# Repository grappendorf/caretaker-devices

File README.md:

Caretaker Smart Home Server Devices
===================================

Caretaker is a DIY smart home project. The aim is to create a totally wireless and scaleable system to control 
power switches (lamps and other electrical appliances) and measure values like temperatures, brightness and power 
consumption. All devices should be controllable through local devices as well as mobile devices over the internet. 
The goal is to use WiFly WLAN modules in every device. This allows for a bi-directional communication between all 
devices, so besides controlling a device it can itself send asynchronous status update messages, i.e. pressing a 
physical button on a dimmer to switch a lamp on, will also update a button in a remote control application, 
eliminating the need for periodically polling the device status

This project contains the firmware and Eagle PCB schematics and layouts for the various Caretaker devices.

Licenses
--------

The firmare source code is licensed under the MIT license.
The hardware is licensed under the CERN Open Hardware Licence v1.2.

Third Party Libraries
----------------------

The following Arduino libraries are included into this project:

* Adafruit_MAX31855
	https://github.com/adafruit/Adafruit-MAX31855-library
	BSD
* Bounce 
  http://www.arduino.cc/playground/Code/Bounce  
  LGPL3
* ClickEncoder
  https://github.com/0xPIT/encoder
  MIT
* CmdMessenger
  http://playground.arduino.cc//Code/CmdMessenger
  MIT
* DallasTemperature
  http://milesburton.com/Dallas_Temperature_Control_Library   
  GPL2 
* EasyVr
	https://github.com/RoboTech-srl/EasyVR-Arduino
	MIT
* EEPROMex
  http://thijs.elenbaas.net/2012/07/extended-eeprom-library-for-arduino/
  LGPL
* LiquidCrystal440
  https://code.google.com/p/liquidcrystal440/
  GPL3
* MultiMap
  http://playground.arduino.cc/Main/MultiMap
  MIT?
* OneWire
  http://www.pjrc.com/teensy/td_libs_OneWire.html
  CUSTOM
* PID
  http://playground.arduino.cc/Code/PIDLibrary
  GPL3
* PinChangeInt
  http://arduino.cc/playground/Main/PinChangeInt
  GPL3
* RunningAverage
  http://playground.arduino.cc/Main/runningAverage
  MIT?
* TimerOne
  http://arduino.cc/playground/Code/Timer1
  GPL3
* WiFly
	https://github.com/Seeed-Studio/WiFi_Shield
	MIT?

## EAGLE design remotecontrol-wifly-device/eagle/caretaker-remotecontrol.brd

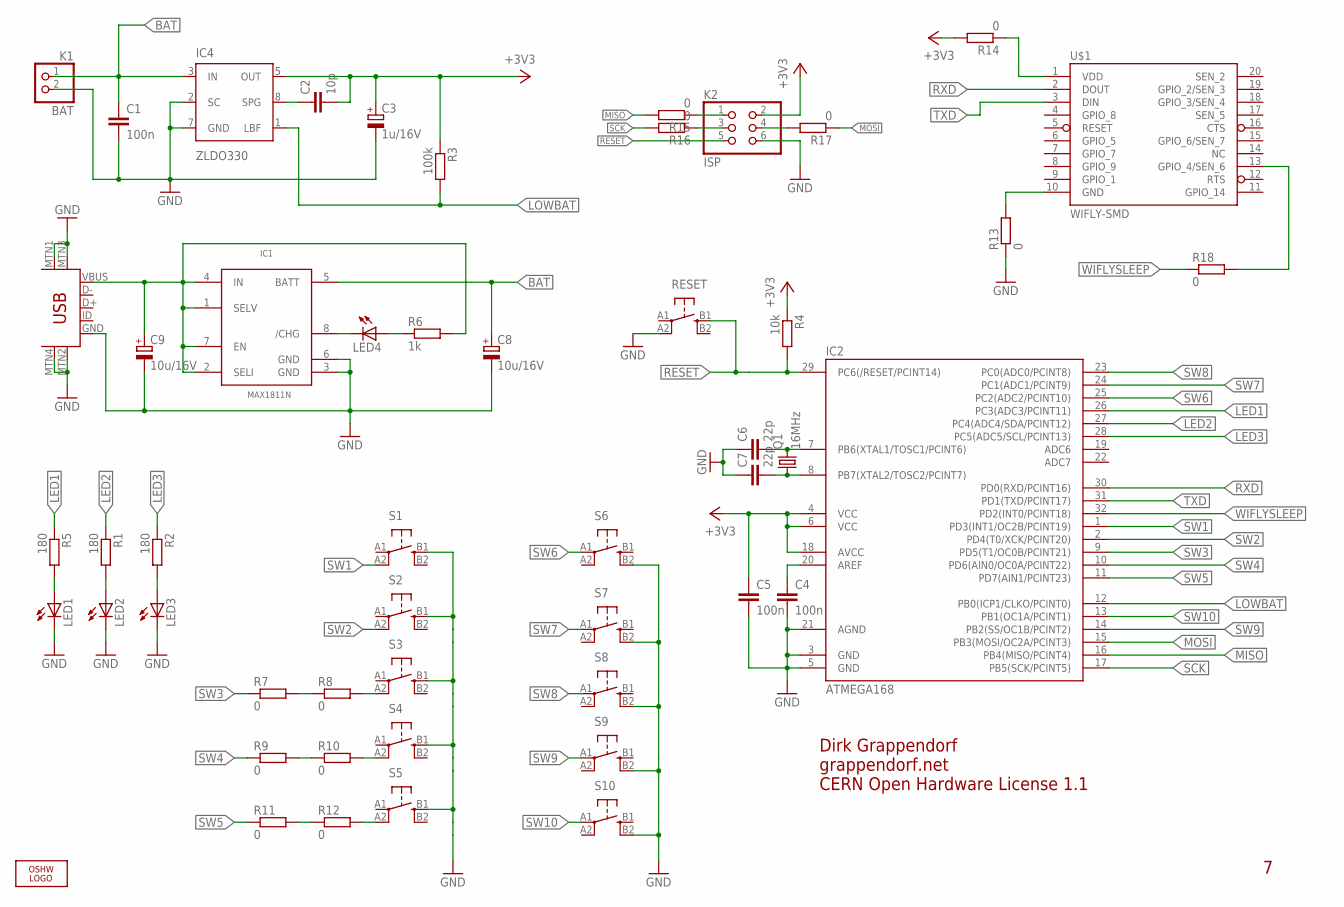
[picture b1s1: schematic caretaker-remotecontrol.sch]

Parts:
C1, C4, C5: 100n; C1206
C2: 10p; C1206
C3: 1u/16V; PANASONIC_B
C6, C7: 22p; C1206
C8, C9: 10u/16V; PANASONIC_B
IC1: MAX1811N; SO08
IC2: ATMEGA168; TQFP32-08
IC4: ZLDO330; SM8
K1: BAT; 1X02
K2: ISP; 2X03/90
K3: USB-MINIB-5PIN; USB-MINIB
LED1, LED2, LED3, LED4: LEDKA-3528ASYC; KA-3528ASYC
LOGO1: OSHW_LOGO_10MILX0350-NT; OSHW_10X350_NOTEXT
Q1: 16MHz; HC49UP
R1, R2, R5: 180; R1206
R3: 100k; R1206
R4: 10k; R1206
R6: 1k; R1206
R7, R8, R9, R10, R11, R12, R13, R14, R15, R16, R17, R18: 0; R1206
RESET: TAC_SWITCHSMD-BIG; TACTILE_SWITCH_TALL
S1, S2, S3, S4, S5, S6, S7, S8, S9, S10: TAC_SWITCHSMD-BIG; TACTILE_SWITCH_TALL
U$1: WIFLY-SMD

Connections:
+3V3: C2.2, C3.+, C5.1, IC2.4 (VCC), IC2.6 (VCC), IC2.18 (AVCC), IC4.5 (OUT), K2.2, R3.1, R4.1, R14.2
BAT: C1.1, C8.+, IC1.5 (BATT), IC4.3 (IN), K1.1
GND: C1.2, C3.-, C4.2, C5.2, C6.1, C7.1, C8.-, C9.-, IC1.3 (GND), IC1.6 (GND), IC2.3 (GND), IC2.5 (GND), IC2.21 (AGND), IC4.2 (SC), IC4.7 (GND), K1.2, K2.6, K3.GND, K3.MTN1 (MTN2), K3.MTN2 (MTN3), K3.MTN3 (MTN1), K3.MTN4, LED1.C, LED2.C, LED3.C, R13.1, RESET.A2 (2), S1.B1 (3), S2.B1 (3), S3.B1 (3), S4.B1 (3), S5.B1 (3), S6.B2 (4), S7.B2 (4), S8.B2 (4), S9.B2 (4), S10.B2 (4)
LED1: IC2.26 (PC3(ADC3/PCINT11)), R5.1
LED2: IC2.27 (PC4(ADC4/SDA/PCINT12)), R1.1
LED3: IC2.28 (PC5(ADC5/SCL/PCINT13)), R2.1
LOWBAT: IC2.12 (PB0(ICP1/CLKO/PCINT0)), IC4.1 (LBF), R3.2
MISO: IC2.16 (PB4(MISO/PCINT4)), R15.2
MOSI: IC2.15 (PB3(MOSI/OC2A/PCINT3)), R17.1
unnamed: C9.+, IC1.1 (SELV), IC1.2 (SELI), IC1.4 (IN), IC1.7 (EN), K3.VBUS, R6.2
unnamed: C4.1, IC2.20 (AREF)
unnamed: C6.2, IC2.7 (PB6(XTAL1/TOSC1/PCINT6)), Q1.2
unnamed: C7.2, IC2.8 (PB7(XTAL2/TOSC2/PCINT7)), Q1.1
unnamed: LED2.A, R1.2
unnamed: LED3.A, R2.2
unnamed: LED4.A, R6.1
unnamed: LED1.A, R5.2
unnamed: IC1.8 (/CHG), LED4.C
unnamed: C2.1, IC4.8 (SPG)
unnamed: R8.2, S3.A2 (2)
unnamed: R10.2, S4.A2 (2)
unnamed: R12.2, S5.A2 (2)
unnamed: R7.2, R8.1
unnamed: R9.2, R10.1
unnamed: R11.2, R12.1
unnamed: R13.2, U$1.10 (GND)
unnamed: R14.1, U$1.1 (VDD)
unnamed: K2.1, R15.1
unnamed: K2.3, R16.1
unnamed: K2.4, R17.2
unnamed: R18.2, U$1.13 (GPIO_4/SEN_6)
RESET: IC2.29 (PC6(/RESET/PCINT14)), K2.5, R4.2, RESET.B1 (3)
RXD: IC2.30 (PD0(RXD/PCINT16)), U$1.2 (DOUT)
SCK: IC2.17 (PB5(SCK/PCINT5)), R16.2
SW1: IC2.1 (PD3(INT1/OC2B/PCINT19)), S1.A2 (2)
SW2: IC2.2 (PD4(T0/XCK/PCINT20)), S2.A2 (2)
SW3: IC2.9 (PD5(T1/OC0B/PCINT21)), R7.1
SW4: IC2.10 (PD6(AIN0/OC0A/PCINT22)), R9.1
SW5: IC2.11 (PD7(AIN1/PCINT23)), R11.1
SW6: IC2.25 (PC2(ADC2/PCINT10)), S6.A1 (1)
SW7: IC2.24 (PC1(ADC1/PCINT9)), S7.A1 (1)
SW8: IC2.23 (PC0(ADC0/PCINT8)), S8.A1 (1)
SW9: IC2.14 (PB2(SS/OC1B/PCINT2)), S9.A1 (1)
SW10: IC2.13 (PB1(OC1A/PCINT1)), S10.A1 (1)
TXD: IC2.31 (PD1(TXD/PCINT17)), U$1.3 (DIN)
WIFLYSLEEP: IC2.32 (PD2(INT0/PCINT18)), R18.1

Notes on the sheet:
Dirk Grappendorf
grappendorf.net
CERN Open Hardware License 1.1

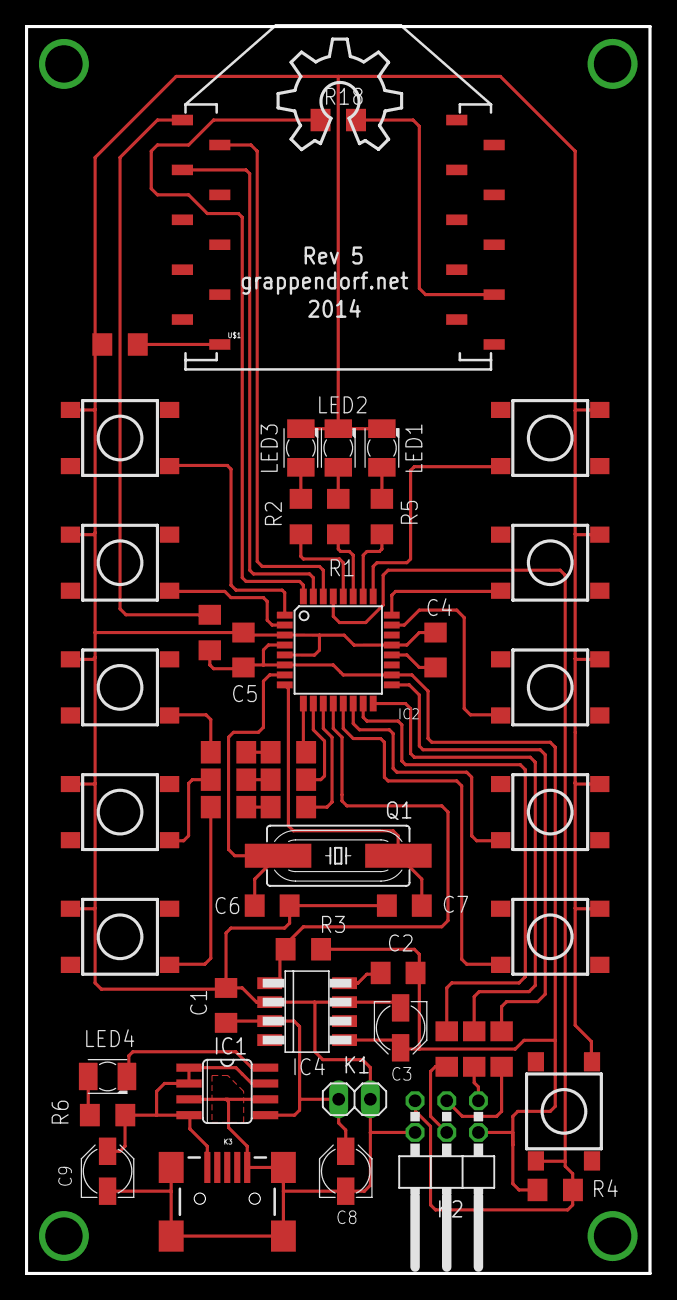
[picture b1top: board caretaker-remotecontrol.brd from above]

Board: 2 copper layers, 50.0 x 100.0 mm, 51 parts (0 on the bottom side), 46 nets.

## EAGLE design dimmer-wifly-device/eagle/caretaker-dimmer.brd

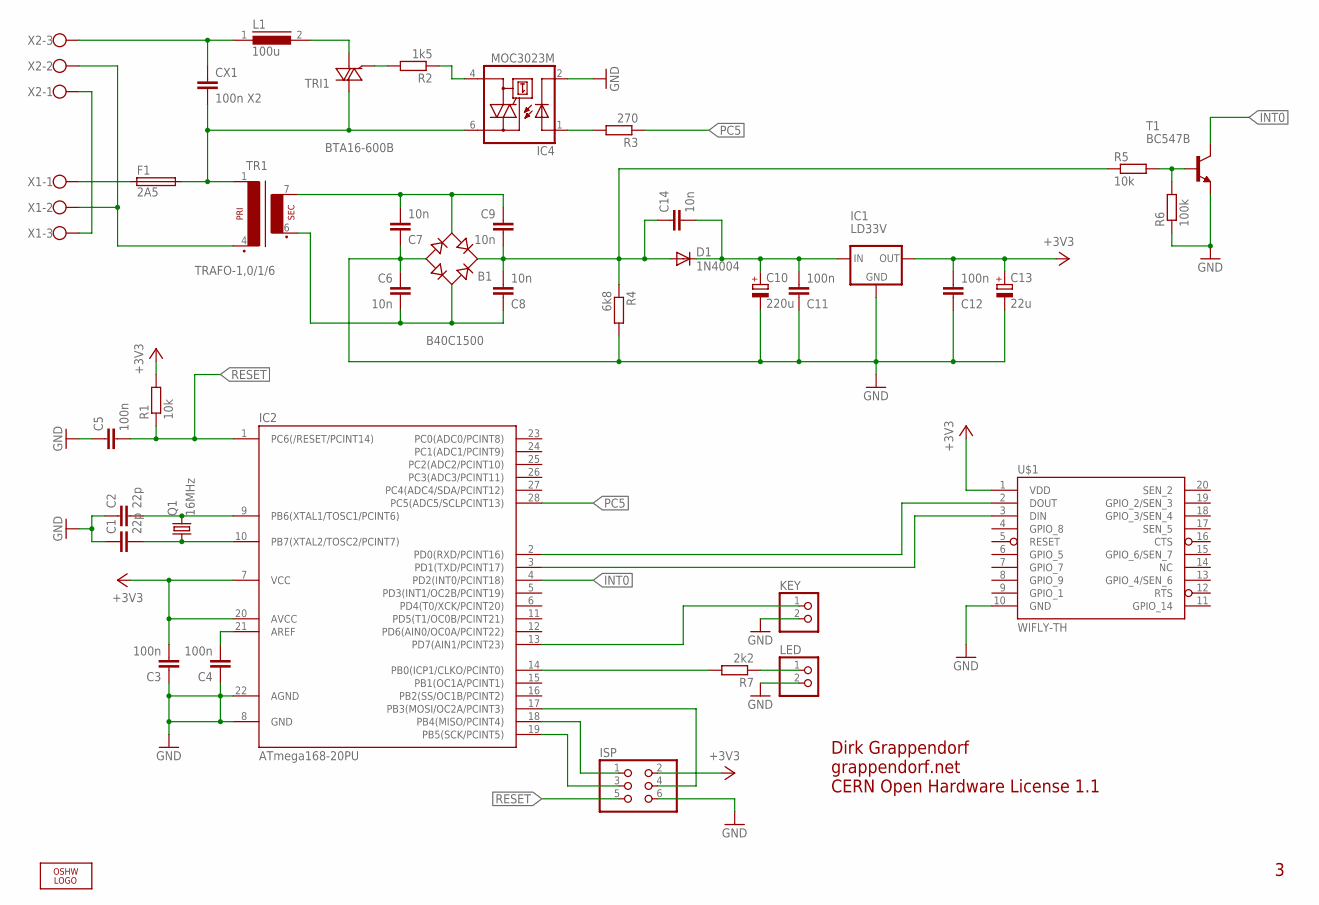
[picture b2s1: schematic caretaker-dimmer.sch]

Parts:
B1: B40C1500; 2KBB
C1, C2: 22p; C025-025X050
C3, C4, C5, C11, C12: 100n; C025-024X044
C6, C7, C8, C9, C14: 10n; C025-024X044
C10: 220u; E3,5-8
C13: 22u; E2,5-5
CX1: 100n X2; XC15B10
D1: 1N4004; D-10
F1: 2A5; SH22,5
IC1: LD33V; 78XXL
IC2: ATmega168-20PU; DIL28-3
IC4: MOC3023M; DIL06
ISP: PINHD-2X3; 2X03
KEY: PINHD-1X2; 1X02
L1: 100u; ED22
LED: PINHD-1X2; 1X02
LOGO1: OSHW_LOGO_10MILX0350-NT-BOTTOM; OSHW_10X350_NOTEXT_BOTTOM
Q1: 16MHz; HC49U-V
R1, R5: 10k; 0204/7
R2: 1k5; 0204/7
R3: 270; 0204/7
R4: 6k8; 0204/7
R6: 100k; 0204/7
R7: 2k2; 0204/7
T1: BC547B; TO92
TR1: TRAFO-1,0/1/6
TRI1: BTA16-600B; TO220AB
U$1: WIFLY-TH
X1, X2: W237-103

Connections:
+3V3: C3.2, C12.2, C13.+, IC1.GND (OUT), IC2.7 (VCC), IC2.20 (AVCC), ISP.2, R1.2, U$1.1 (VDD)
GND: B1.-, C1.1, C2.1, C3.1, C4.1, C5.1, C6.1, C7.1, C10.-, C11.1, C12.1, C13.-, IC1.IN (GND), IC2.8 (GND), IC2.22 (AGND), IC4.2 (C), ISP.6, KEY.2, LED.2, R4.2, R6.1, T1.1 (E), U$1.10 (GND)
INT0: IC2.4 (PD2(INT0/PCINT18)), T1.3 (C)
unnamed: C2.2, IC2.9 (PB6(XTAL1/TOSC1/PCINT6)), Q1.2
unnamed: C1.2, IC2.10 (PB7(XTAL2/TOSC2/PCINT7)), Q1.1
unnamed: C4.2, IC2.21 (AREF)
unnamed: LED.1, R7.1
unnamed: B1.AC1, C6.2, C8.1, TR1.6 (S3)
unnamed: R2.2, TRI1.3 (G)
unnamed: C10.+, C11.2, C14.2, D1.C, IC1.OUT (IN)
unnamed: B1.AC2, C7.2, C9.1, TR1.7 (S4)
unnamed: CX1.1, L1.1, X2.3
unnamed: F1.1, X1.1
unnamed: L1.2, TRI1.1 (A1)
unnamed: CX1.2, F1.2, IC4.6 (A2), TR1.1, TRI1.2 (A2)
unnamed: TR1.4 (P2), X1.2, X2.2
unnamed: IC4.4 (A1), R2.1
unnamed: IC4.1 (A), R3.2
unnamed: IC2.2 (PD0(RXD/PCINT16)), U$1.2 (DOUT)
unnamed: IC2.13 (PD7(AIN1/PCINT23)), KEY.1
unnamed: R5.2, R6.2, T1.2 (B)
unnamed: IC2.18 (PB4(MISO/PCINT4)), ISP.1
unnamed: IC2.19 (PB5(SCK/PCINT5)), ISP.3
unnamed: IC2.17 (PB3(MOSI/OC2A/PCINT3)), ISP.4
unnamed: IC2.14 (PB0(ICP1/CLKO/PCINT0)), R7.2
unnamed: X1.3, X2.1
unnamed: IC2.3 (PD1(TXD/PCINT17)), U$1.3 (DIN)
unnamed: B1.+, C8.2, C9.2, C14.1, D1.A, R4.1, R5.1
PC5: IC2.28 (PC5(ADC5/SCLPCINT13)), R3.1
RESET: C5.2, IC2.1 (PC6(/RESET/PCINT14)), ISP.5, R1.1

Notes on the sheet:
Dirk Grappendorf
grappendorf.net
CERN Open Hardware License 1.1

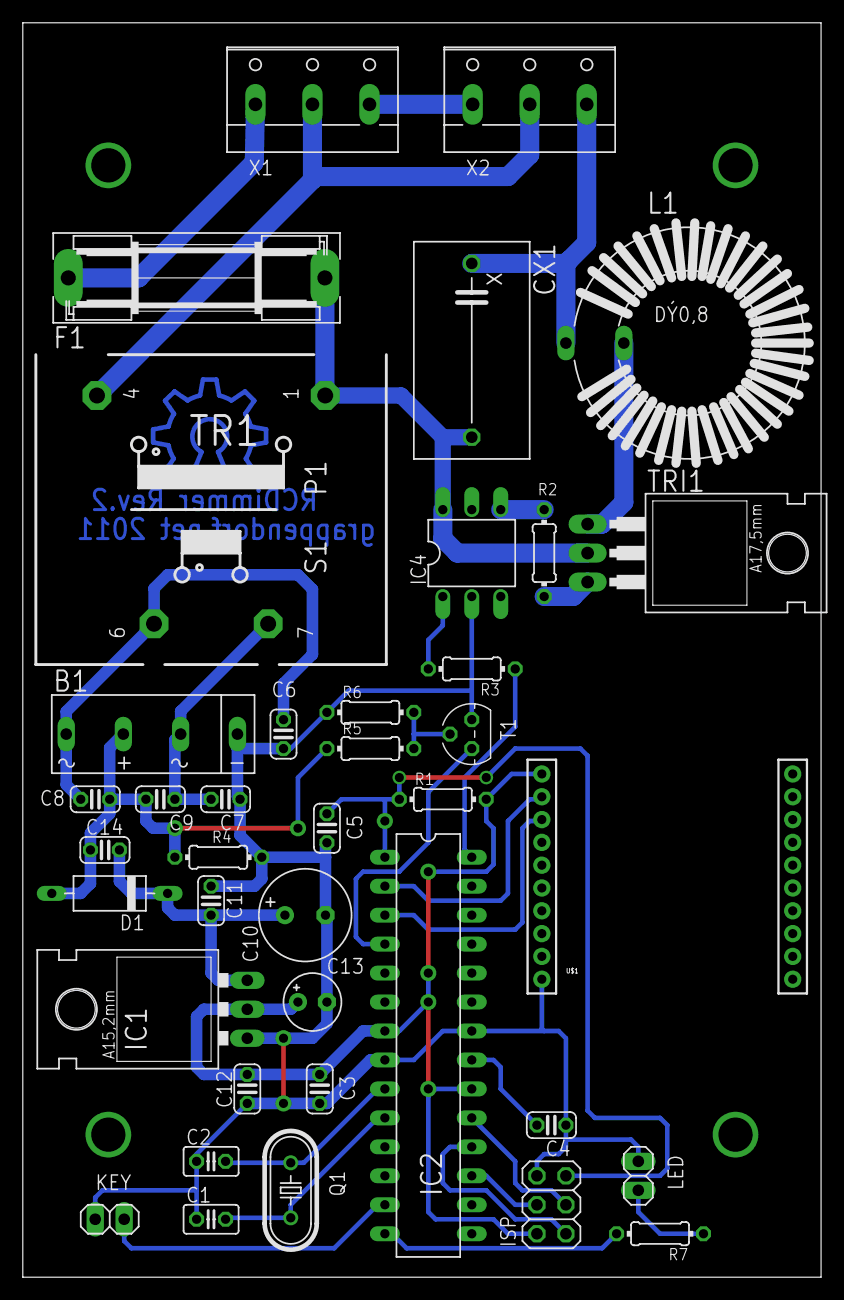
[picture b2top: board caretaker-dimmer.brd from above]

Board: 2 copper layers, 70.0 x 110.0 mm, 40 parts (0 on the bottom side), 30 nets.

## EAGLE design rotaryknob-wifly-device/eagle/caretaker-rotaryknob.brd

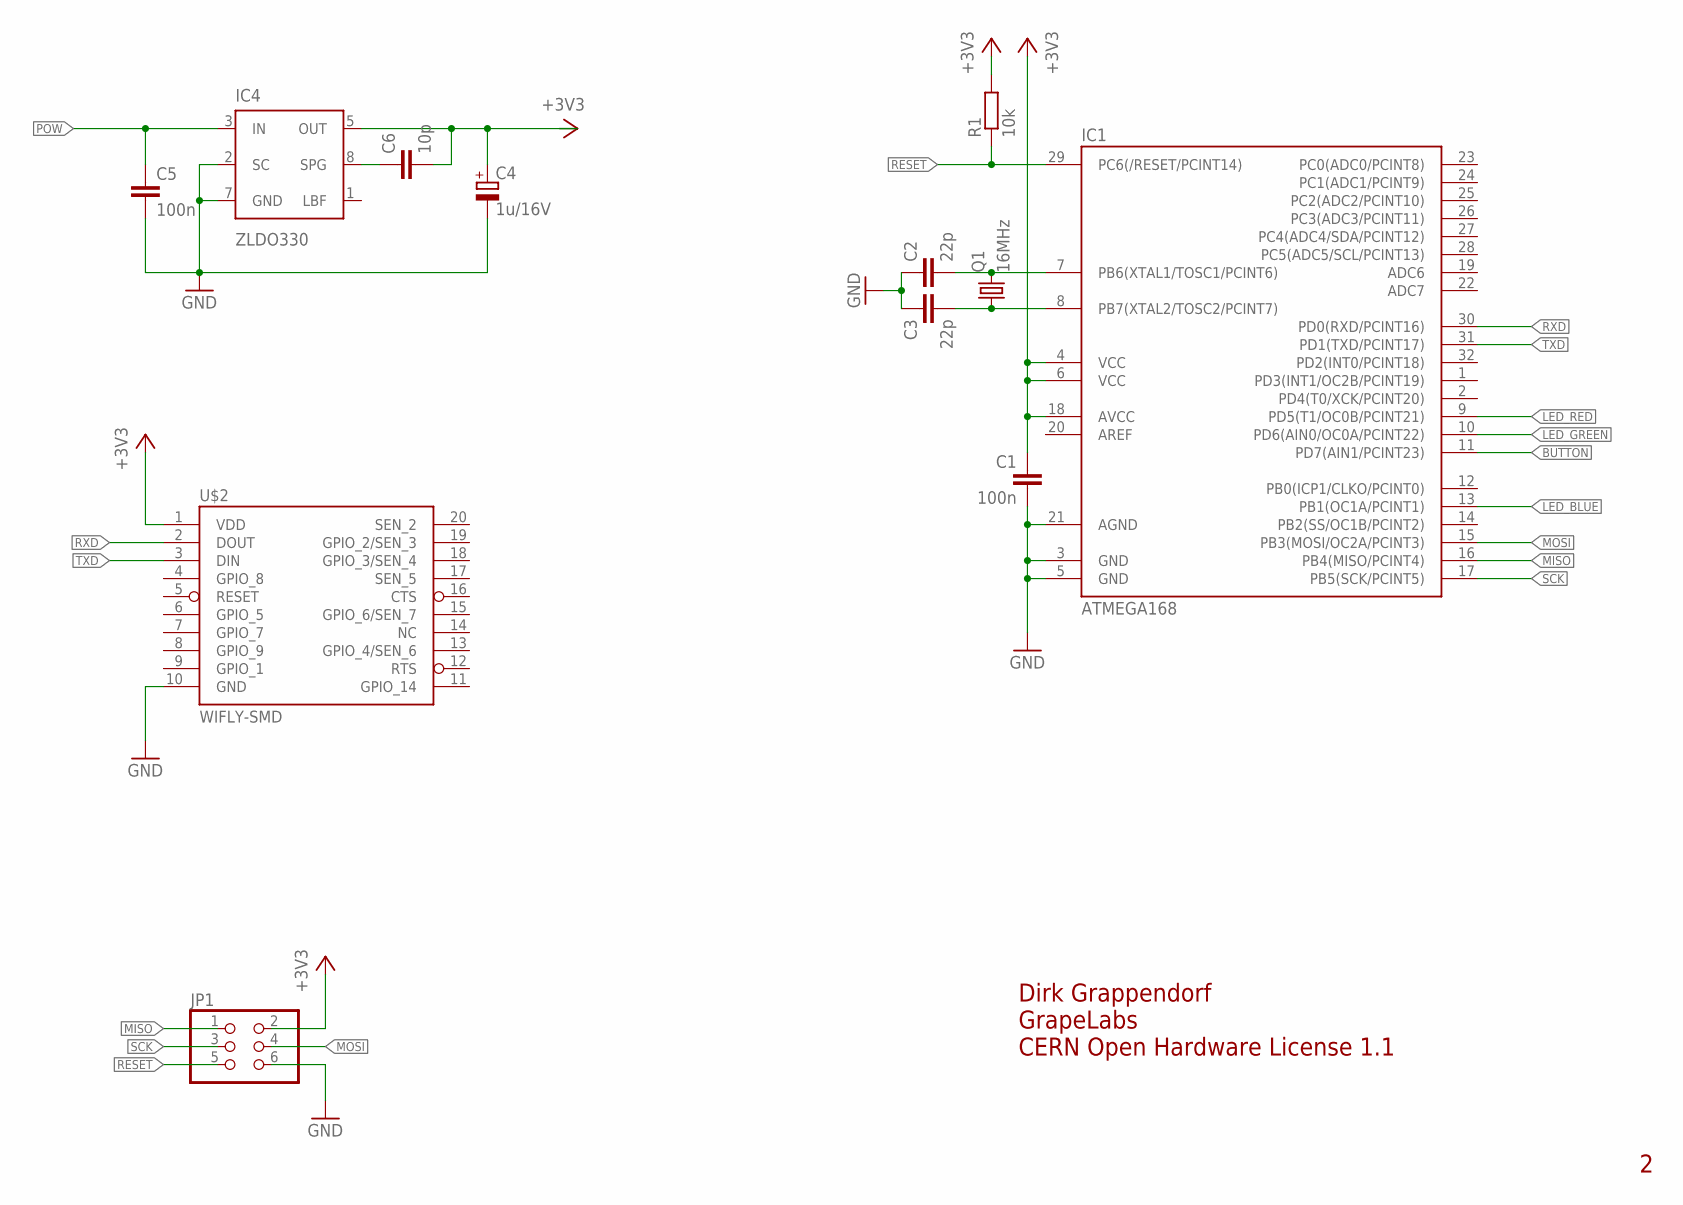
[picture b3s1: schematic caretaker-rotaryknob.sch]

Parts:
C1: 100n; C1206K
C2, C3: 22p; C1206K
C4: 1u/16V; PANASONIC_B
C5: 100n; C1206
C6: 10p; C1206
IC1: ATMEGA168; TQFP32-08
IC4: ZLDO330; SM8
JP1: PINHD-2X3_2.54-SMD; 2X03SMD
Q1: 16MHz; HC49UP
R1: 10k; M1206
U$2: WIFLY-SMD

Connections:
+3V3: C1.1, C4.+, C6.2, IC1.4 (VCC), IC1.6 (VCC), IC1.18 (AVCC), IC4.5 (OUT), JP1.2, R1.2, U$2.1 (VDD)
BUTTON: IC1.11 (PD7(AIN1/PCINT23))
GND: C1.2, C2.1, C3.1, C4.-, C5.2, IC1.3 (GND), IC1.5 (GND), IC1.21 (AGND), IC4.2 (SC), IC4.7 (GND), JP1.6, U$2.10 (GND)
LED_BLUE: IC1.13 (PB1(OC1A/PCINT1))
LED_GREEN: IC1.10 (PD6(AIN0/OC0A/PCINT22))
LED_RED: IC1.9 (PD5(T1/OC0B/PCINT21))
MISO: IC1.16 (PB4(MISO/PCINT4)), JP1.1
MOSI: IC1.15 (PB3(MOSI/OC2A/PCINT3)), JP1.4
unnamed: C2.2, IC1.7 (PB6(XTAL1/TOSC1/PCINT6)), Q1.2
unnamed: C3.2, IC1.8 (PB7(XTAL2/TOSC2/PCINT7)), Q1.1
unnamed: C6.1, IC4.8 (SPG)
POW: C5.1, IC4.3 (IN)
RESET: IC1.29 (PC6(/RESET/PCINT14)), JP1.5, R1.1
RXD: IC1.30 (PD0(RXD/PCINT16)), U$2.2 (DOUT)
SCK: IC1.17 (PB5(SCK/PCINT5)), JP1.3
TXD: IC1.31 (PD1(TXD/PCINT17)), U$2.3 (DIN)

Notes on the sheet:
Dirk Grappendorf
GrapeLabs
CERN Open Hardware License 1.1

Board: 2 copper layers, 12 parts (0 on the bottom side), 12 nets, no tracks yet.

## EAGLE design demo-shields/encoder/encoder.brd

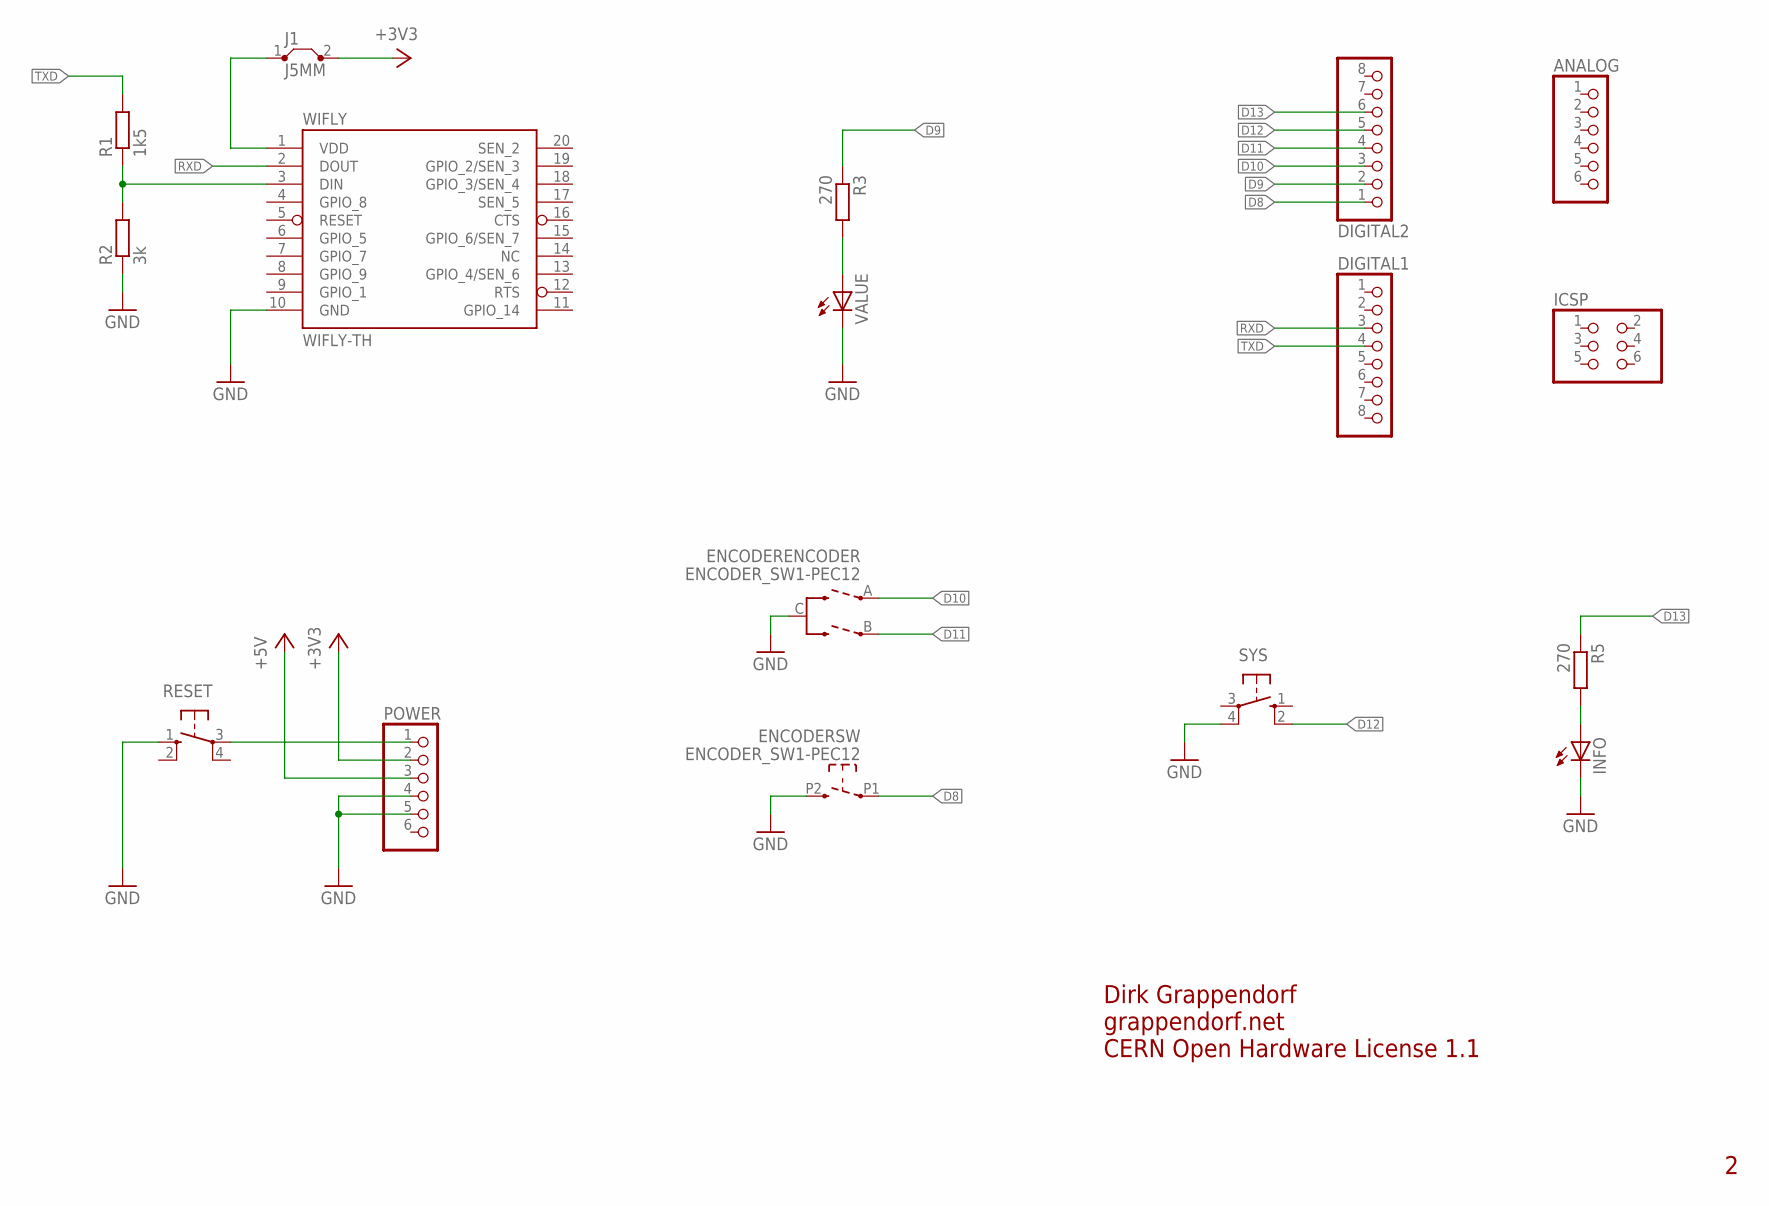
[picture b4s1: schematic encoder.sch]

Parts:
ANALOG: PINHD-1X6; 1X06
DIGITAL1: PINHD-1X8TH; 1X08-TH
DIGITAL2: PINHD-1X8_2.54; 1X08
ENCODER: ENCODER_SW1-PEC12; PEC12_INCREMENTAL_ENCODER
ICSP: PINHD-2X3; 2X03
INFO: LED3MM
J1: J5MM; 05
POWER: PINHD-1X6_2.54; 1X06
R1: 1k5; 0204/7
R2: 3k; 0204/7
R3, R5: 270; 0204/7
RESET: 10-XX; B3F-10XX
SYS: 10-XX; B3F-10XX
VALUE: LED3MM
WIFLY: WIFLY-TH

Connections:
+3V3: J1.2, POWER.2
+5V: POWER.3
D8: DIGITAL2.1, ENCODER.P1 (1)
D9: DIGITAL2.2, R3.1
D10: DIGITAL2.3, ENCODER.A
D11: DIGITAL2.4, ENCODER.B
D12: DIGITAL2.5, SYS.2 (S1)
D13: DIGITAL2.6, R5.1
GND: ENCODER.C, ENCODER.P2 (2), INFO.K (C), POWER.4, POWER.5, R2.1, RESET.1 (S), SYS.4 (P1), VALUE.K (C), WIFLY.10 (GND)
unnamed: R1.1, R2.2, WIFLY.3 (DIN)
unnamed: POWER.1, RESET.3
unnamed: J1.1, WIFLY.1 (VDD)
unnamed: R3.2, VALUE.A
unnamed: INFO.A, R5.2
RXD: DIGITAL1.3, WIFLY.2 (DOUT)
TXD: DIGITAL1.4, R1.2

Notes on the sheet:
Dirk Grappendorf
grappendorf.net
CERN Open Hardware License 1.1

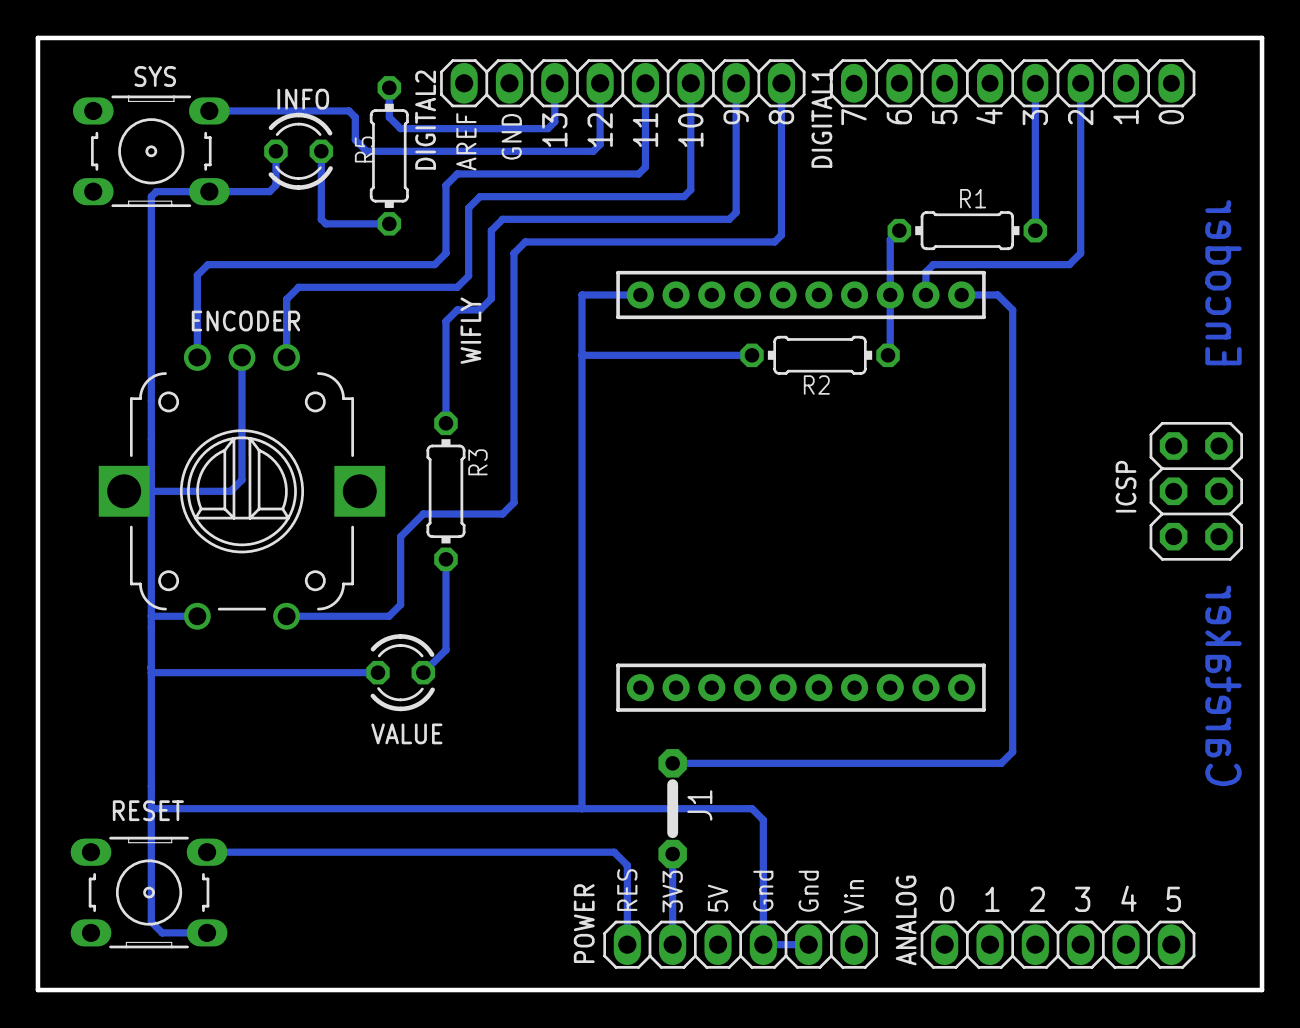
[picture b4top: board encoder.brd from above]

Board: 2 copper layers, 68.6 x 53.3 mm, 16 parts (0 on the bottom side), 15 nets.

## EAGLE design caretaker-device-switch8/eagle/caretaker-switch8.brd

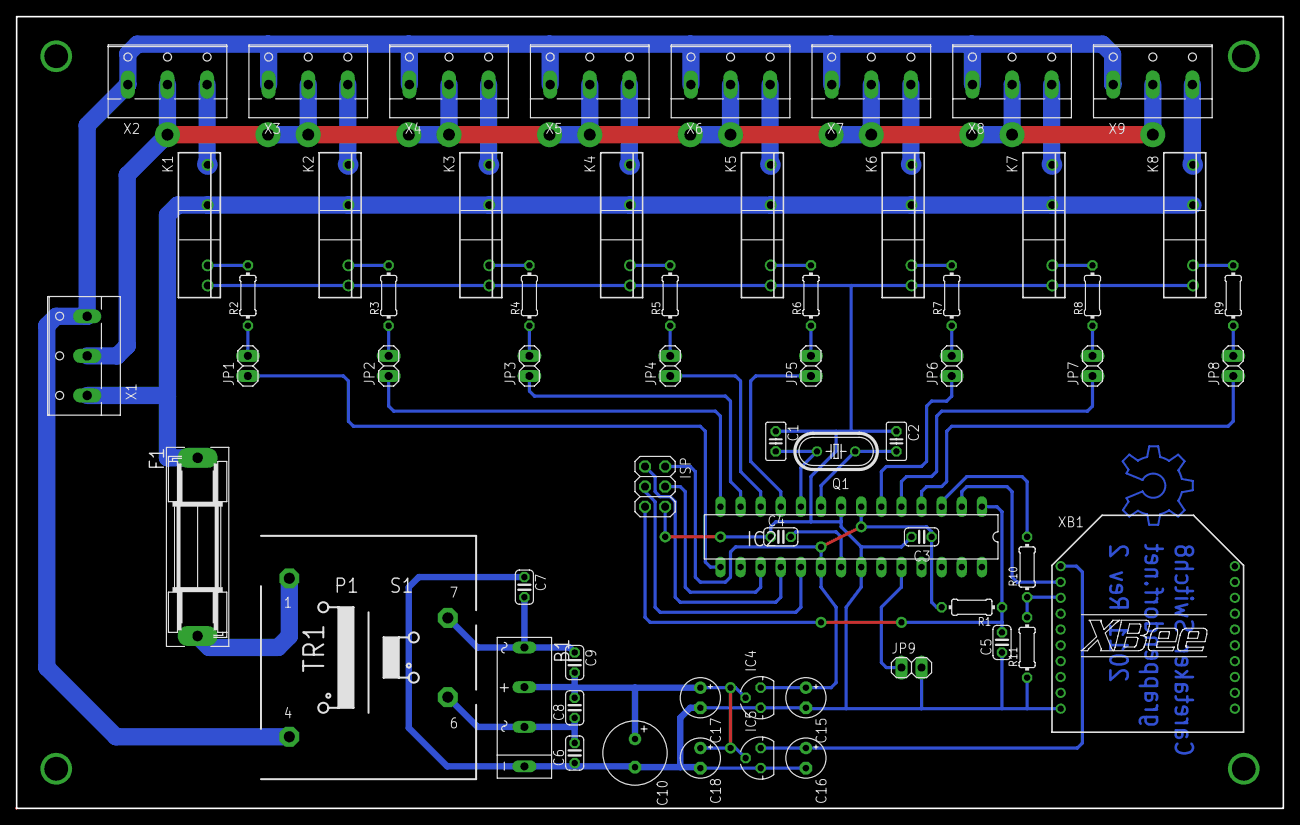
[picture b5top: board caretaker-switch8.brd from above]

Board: 2 copper layers, 160.0 x 100.0 mm, 61 parts (0 on the bottom side), 53 nets.

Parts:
B1: B40C1500; 2KBB
C1, C2: 22p; C025-025X050
C3, C4, C5: 100n; C025-024X044
C6, C7, C8, C9: 10n; C025-024X044
C10: 220u; E3,5-8
C15, C16, C17, C18: 1u; E2,5-5
F1: 2A; SH22,5
IC2: ATmega168-20PU; DIL28-3
IC4: MCP1702-5002; MCP1702
IC5: MCP1702-3302; MCP1702
ISP: 2X03
JP1: LED1; 1X02
JP2: LED2; 1X02
JP3: LED3; 1X02
JP4: LED4; 1X02
JP5: LED5; 1X02
JP6: LED6; 1X02
JP7: LED7; 1X02
JP8: LED8; 1X02
JP9: BUZZER; 1X02
K1, K2, K3, K4, K5, K6, K7, K8: S202S02
LOGO1: OSHW_LOGO_10MILX0350-NT-BOTTOM; OSHW_10X350_NOTEXT_BOTTOM
Q1: 16MHz; HC49U-V
R1, R10: 10k; 0204/7
R2, R3, R4, R5, R6, R7, R8, R9: 120; 0204/7
R11: 15k; 0204/7
TR1: TRAFO-1,0/1/6
X1, X2, X3, X4, X5, X6, X7, X8, X9: W237-103
XB1: XBEE

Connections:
+3V3: C16.+, IC5.VOUT, XB1.1
+5V: C3.2, C15.+, IC2.7, IC2.20, IC4.VOUT, ISP.2, R1.2
GND: B1.-, C1.1, C2.1, C3.1, C4.1, C5.1, C6.1, C7.1, C10.-, C15.-, C16.-, C17.-, C18.-, IC2.8, IC2.22, IC4.GND, IC5.GND, ISP.6, JP9.2, K1.4, K2.4, K3.4, K4.4, K5.4, K6.4, K7.4, K8.4, R11.1, XB1.10
unnamed: C2.2, IC2.9, Q1.2
unnamed: C1.2, IC2.10, Q1.1
unnamed: C4.2, IC2.21
unnamed: IC2.18, ISP.1
unnamed: IC2.24, JP9.1
unnamed: IC2.19, ISP.3
unnamed: K1.1, X2.3
unnamed: K2.1, X3.3
unnamed: K3.1, X4.3
unnamed: K4.1, X5.3
unnamed: B1.AC1, C7.2, C9.1, TR1.7
unnamed: K5.1, X6.3
unnamed: B1.+, C8.2, C9.2, C10.+, C17.+, C18.+, IC4.VIN, IC5.VIN
unnamed: K6.1, X7.3
unnamed: K7.1, X8.3
unnamed: K8.1, X9.3
unnamed: JP1.2, R2.1
unnamed: K1.3, R2.2
unnamed: JP2.2, R3.1
unnamed: K2.3, R3.2
unnamed: IC2.17, ISP.4
unnamed: JP3.2, R4.1
unnamed: K3.3, R4.2
unnamed: JP4.2, R5.1
unnamed: K4.3, R5.2
unnamed: JP5.2, R6.1
unnamed: K5.3, R6.2
unnamed: JP6.2, R7.1
unnamed: K6.3, R7.2
unnamed: JP7.2, R8.1
unnamed: K7.3, R8.2
unnamed: JP8.2, R9.1
unnamed: K8.3, R9.2
unnamed: F1.2, TR1.1
unnamed: R10.1, R11.2, XB1.3
unnamed: B1.AC2, C6.2, C8.1, TR1.6
POW-N: TR1.4, X1.3, X2.1, X3.1, X4.1, X5.1, X6.1, X7.1, X8.1, X9.1
POW-P: F1.1, K1.2, K2.2, K3.2, K4.2, K5.2, K6.2, K7.2, K8.2, X1.1
POW-S: X1.2, X2.2, X3.2, X4.2, X5.2, X6.2, X7.2, X8.2, X9.2
RESET: C5.2, IC2.1, ISP.5, R1.1
RXD: IC2.2, XB1.2
S1: IC2.15, JP1.1
S2: IC2.14, JP2.1
S3: IC2.13, JP3.1
S4: IC2.12, JP4.1
S5: IC2.11, JP5.1
S6: IC2.6, JP6.1
S7: IC2.5, JP7.1
S8: IC2.4, JP8.1
TXD: IC2.3, R10.2

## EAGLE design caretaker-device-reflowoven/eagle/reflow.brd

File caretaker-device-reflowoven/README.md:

Caretaker Reflow Oven Device
============================

Caretaker Reflow Oven controller.

Licenses
--------

### Caretaker

The Caretaker code is licensed under the the MIT License
You find a copy of license in the root directory of this project

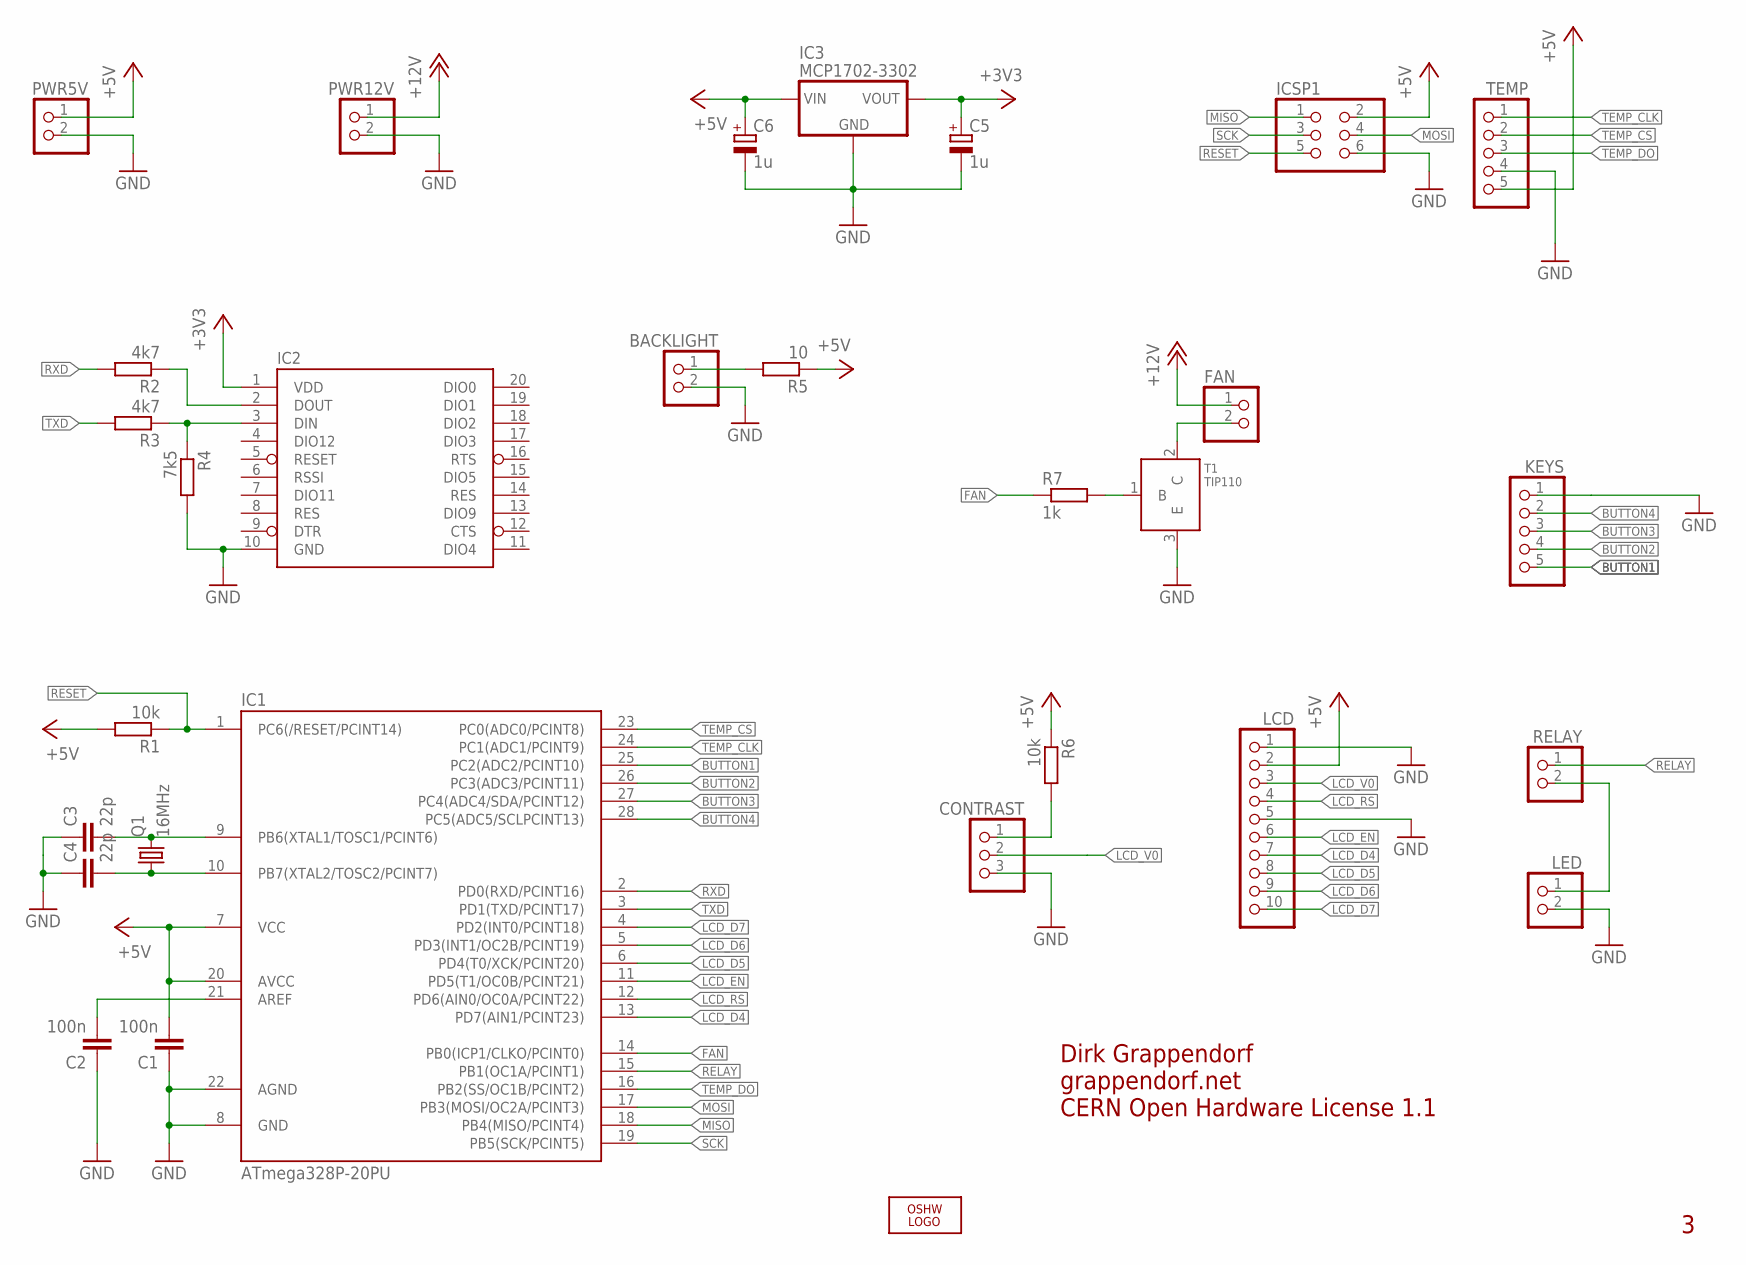
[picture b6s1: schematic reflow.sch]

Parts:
BACKLIGHT: PINHD-1X2; 1X02
C1, C2: 100n; C025-024X044
C3, C4: 22p; C025-025X050
C5, C6: 1u; E2,5-5
CONTRAST: PINHD-1X3; 1X03
FAN: PINHD-1X2; 1X02
IC1: ATmega328P-20PU; DIL28-3
IC2: XBEE-1B1; XBEE-1
IC3: MCP1702-3302; MCP1702
ICSP1: PINHD-2X03_2.54; 2X03
KEYS: PINHD-1X5; 1X05
LCD: PINHD-1X10; 1X10
LED: PINHD-1X2; 1X02
LOGO1: OSHW_LOGO_10MILX0350-NT-BOTTOM; OSHW_10X350_NOTEXT_BOTTOM
PWR5V, PWR12V: PINHD-1X2; 1X02
Q1: 16MHz; HC49U-V
R1, R6: 10k; 0204/7
R2, R3: 4k7; 0204/7
R4: 7k5; 0204/7
R5: 10; 0204/7
R7: 1k; 0204/7
RELAY: PINHD-1X2; 1X02
T1: TIP110; T0220
TEMP: PINHD-1X5; 1X05

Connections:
+3V3: C5.+, IC2.1 (VDD), IC3.VOUT (OUT)
+5V: C1.2, C6.+, IC1.7 (VCC), IC1.20 (AVCC), IC3.VIN (IN), ICSP1.2, LCD.2, PWR5V.1, R1.2, R5.1, R6.1, TEMP.5
+12V: FAN.1, PWR12V.1
BUTTON1: IC1.25 (PC2(ADC2/PCINT10)), KEYS.5
BUTTON2: IC1.26 (PC3(ADC3/PCINT11)), KEYS.4
BUTTON3: IC1.27 (PC4(ADC4/SDA/PCINT12)), KEYS.3
BUTTON4: IC1.28 (PC5(ADC5/SCLPCINT13)), KEYS.2
FAN: IC1.14 (PB0(ICP1/CLKO/PCINT0)), R7.1
GND: BACKLIGHT.2, C1.1, C2.1, C3.1, C4.1, C5.-, C6.-, CONTRAST.3, IC1.8 (GND), IC1.22 (AGND), IC2.10 (GND), IC3.GND, ICSP1.6, KEYS.1, LCD.1, LCD.5, LED.2, PWR5V.2, PWR12V.2, R4.2, T1.3 (E), TEMP.4
LCD_D4: IC1.13 (PD7(AIN1/PCINT23)), LCD.7
LCD_D5: IC1.6 (PD4(T0/XCK/PCINT20)), LCD.8
LCD_D6: IC1.5 (PD3(INT1/OC2B/PCINT19)), LCD.9
LCD_D7: IC1.4 (PD2(INT0/PCINT18)), LCD.10
LCD_EN: IC1.11 (PD5(T1/OC0B/PCINT21)), LCD.6
LCD_RS: IC1.12 (PD6(AIN0/OC0A/PCINT22)), LCD.4
LCD_V0: CONTRAST.2, LCD.3
MISO: IC1.18 (PB4(MISO/PCINT4)), ICSP1.1
MOSI: IC1.17 (PB3(MOSI/OC2A/PCINT3)), ICSP1.4
unnamed: C3.2, IC1.9 (PB6(XTAL1/TOSC1/PCINT6)), Q1.2
unnamed: C4.2, IC1.10 (PB7(XTAL2/TOSC2/PCINT7)), Q1.1
unnamed: C2.2, IC1.21 (AREF)
unnamed: IC2.3 (DIN), R3.1, R4.1
unnamed: IC2.2 (DOUT), R2.1
unnamed: BACKLIGHT.1, R5.2
unnamed: LED.1, RELAY.2
unnamed: CONTRAST.1, R6.2
unnamed: FAN.2, T1.2 (C)
unnamed: R7.2, T1.1 (B)
RELAY: IC1.15 (PB1(OC1A/PCINT1)), RELAY.1
RESET: IC1.1 (PC6(/RESET/PCINT14)), ICSP1.5, R1.1
RXD: IC1.2 (PD0(RXD/PCINT16)), R2.2
SCK: IC1.19 (PB5(SCK/PCINT5)), ICSP1.3
TEMP_CLK: IC1.24 (PC1(ADC1/PCINT9)), TEMP.1
TEMP_CS: IC1.23 (PC0(ADC0/PCINT8)), TEMP.2
TEMP_DO: IC1.16 (PB2(SS/OC1B/PCINT2)), TEMP.3
TXD: IC1.3 (PD1(TXD/PCINT17)), R3.2

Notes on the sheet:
Dirk Grappendorf
grappendorf.net
CERN Open Hardware License 1.1

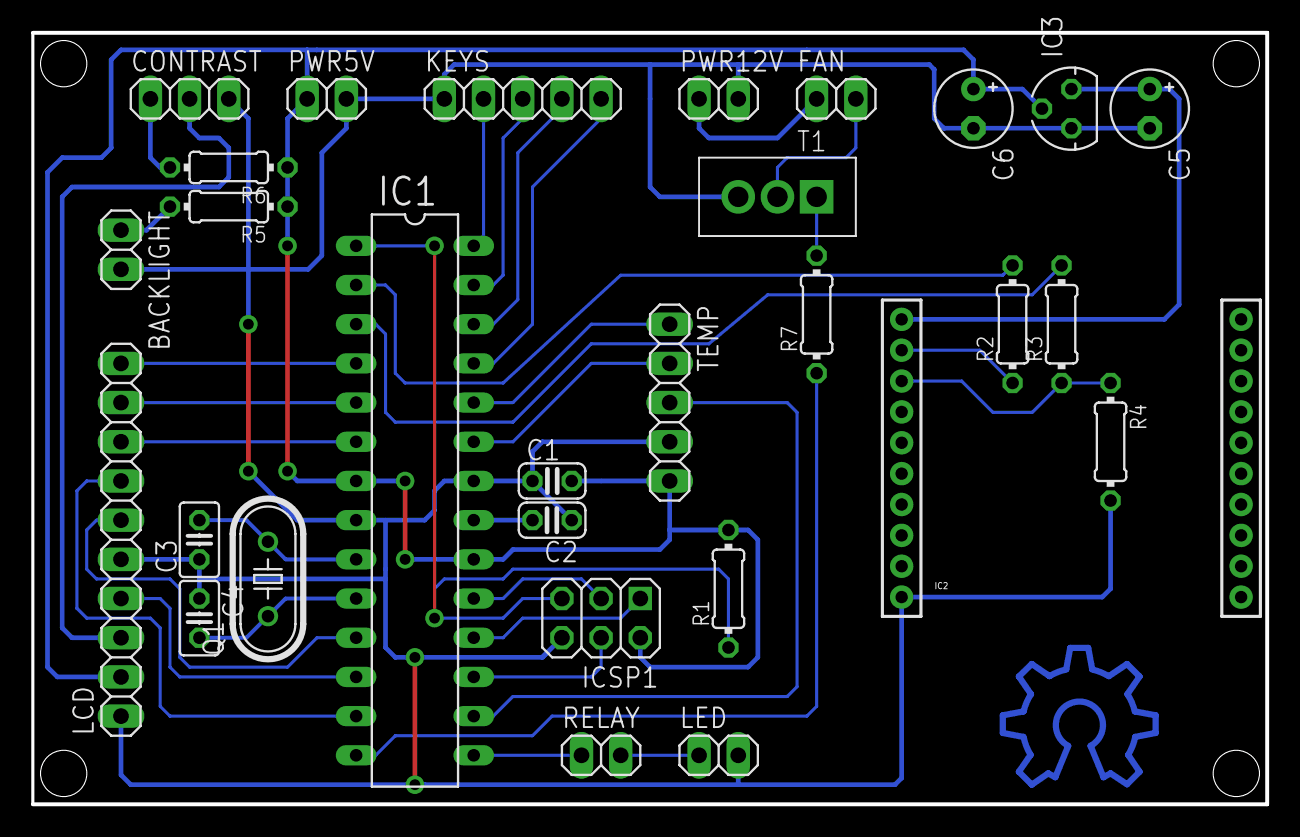
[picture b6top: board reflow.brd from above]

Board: 2 copper layers, 80.0 x 50.0 mm, 30 parts (0 on the bottom side), 36 nets.

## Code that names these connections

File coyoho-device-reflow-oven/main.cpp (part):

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
// IO pins

const uint8_t LCD_RS = 6;
const uint8_t LCD_EN = 5;
const uint8_t LCD_D4 = 7;
const uint8_t LCD_D5 = 4;
const uint8_t LCD_D6 = 3;
const uint8_t LCD_D1 = 2;
const uint8_t BUTTON_1 = 16;
const uint8_t BUTTON_2 = 17;
const uint8_t BUTTON_3 = 18;
const uint8_t BUTTON_4 = 19;
const uint8_t RELAY = 9;
const uint8_t THERMO_DO = 10;
const uint8_t THERMO_CLK = 15;
const uint8_t THERMO_CS = 14;
const uint8_t FAN = 8;

// LCD

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	pinMode(BUTTON_2, INPUT);
	pinMode(BUTTON_3, INPUT);
	pinMode(BUTTON_4, INPUT);
	pinMode(RELAY, OUTPUT);
	pinMode(FAN, OUTPUT);

	digitalWrite(BUTTON_1, HIGH);
	digitalWrite(BUTTON_2, HIGH);
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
